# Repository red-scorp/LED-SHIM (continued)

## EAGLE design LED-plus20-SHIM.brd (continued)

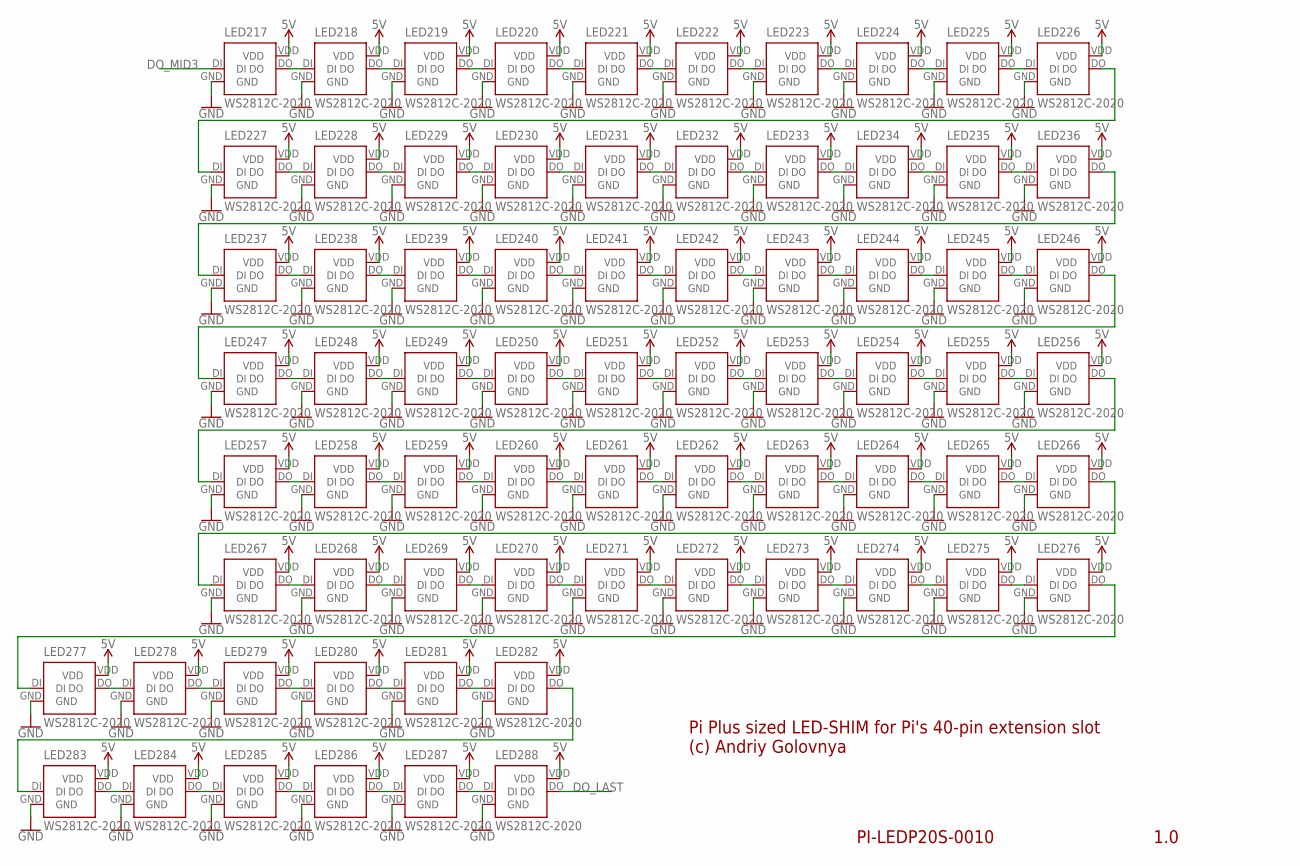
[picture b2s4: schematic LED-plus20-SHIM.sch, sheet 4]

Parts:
LED217, LED218, LED219, LED220, LED221, LED222, LED223, LED224, LED225, LED226, LED227, LED228, LED229, LED230, LED231, LED232, LED233, LED234, LED235, LED236, LED237, LED238, LED239, LED240, LED241, LED242, LED243, LED244, LED245, LED246, LED247, LED248, LED249, LED250, LED251, LED252, LED253, LED254, LED255, LED256, LED257, LED258, LED259, LED260, LED261, LED262, LED263, LED264, LED265, LED266, LED267, LED268, LED269, LED270, LED271, LED272, LED273, LED274, LED275, LED276, LED277, LED278, LED279, LED280, LED281, LED282, LED283, LED284, LED285, LED286, LED287, LED288: WS2812C-2020; WS2812X-2020

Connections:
5V: LED217.VDD, LED218.VDD, LED219.VDD, LED220.VDD, LED221.VDD, LED222.VDD, LED223.VDD, LED224.VDD, LED225.VDD, LED226.VDD, LED227.VDD, LED228.VDD, LED229.VDD, LED230.VDD, LED231.VDD, LED232.VDD, LED233.VDD, LED234.VDD, LED235.VDD, LED236.VDD, LED237.VDD, LED238.VDD, LED239.VDD, LED240.VDD, LED241.VDD, LED242.VDD, LED243.VDD, LED244.VDD, LED245.VDD, LED246.VDD, LED247.VDD, LED248.VDD, LED249.VDD, LED250.VDD, LED251.VDD, LED252.VDD, LED253.VDD, LED254.VDD, LED255.VDD, LED256.VDD, LED257.VDD, LED258.VDD, LED259.VDD, LED260.VDD, LED261.VDD, LED262.VDD, LED263.VDD, LED264.VDD, LED265.VDD, LED266.VDD, LED267.VDD, LED268.VDD, LED269.VDD, LED270.VDD, LED271.VDD, LED272.VDD, LED273.VDD, LED274.VDD, LED275.VDD, LED276.VDD, LED277.VDD, LED278.VDD, LED279.VDD, LED280.VDD, LED281.VDD, LED282.VDD, LED283.VDD, LED284.VDD, LED285.VDD, LED286.VDD, LED287.VDD, LED288.VDD; also elsewhere on the board
DO_LAST: LED288.DO; also elsewhere on the board
DO_MID3: LED217.DI; also elsewhere on the board
GND: LED217.GND, LED218.GND, LED219.GND, LED220.GND, LED221.GND, LED222.GND, LED223.GND, LED224.GND, LED225.GND, LED226.GND, LED227.GND, LED228.GND, LED229.GND, LED230.GND, LED231.GND, LED232.GND, LED233.GND, LED234.GND, LED235.GND, LED236.GND, LED237.GND, LED238.GND, LED239.GND, LED240.GND, LED241.GND, LED242.GND, LED243.GND, LED244.GND, LED245.GND, LED246.GND, LED247.GND, LED248.GND, LED249.GND, LED250.GND, LED251.GND, LED252.GND, LED253.GND, LED254.GND, LED255.GND, LED256.GND, LED257.GND, LED258.GND, LED259.GND, LED260.GND, LED261.GND, LED262.GND, LED263.GND, LED264.GND, LED265.GND, LED266.GND, LED267.GND, LED268.GND, LED269.GND, LED270.GND, LED271.GND, LED272.GND, LED273.GND, LED274.GND, LED275.GND, LED276.GND, LED277.GND, LED278.GND, LED279.GND, LED280.GND, LED281.GND, LED282.GND, LED283.GND, LED284.GND, LED285.GND, LED286.GND, LED287.GND, LED288.GND; also elsewhere on the board
unnamed: LED217.DO, LED218.DI
unnamed: LED218.DO, LED219.DI
unnamed: LED219.DO, LED220.DI
unnamed: LED220.DO, LED221.DI
unnamed: LED221.DO, LED222.DI
unnamed: LED222.DO, LED223.DI
unnamed: LED223.DO, LED224.DI
unnamed: LED224.DO, LED225.DI
unnamed: LED225.DO, LED226.DI
unnamed: LED226.DO, LED227.DI
unnamed: LED227.DO, LED228.DI
unnamed: LED228.DO, LED229.DI
unnamed: LED229.DO, LED230.DI
unnamed: LED230.DO, LED231.DI
unnamed: LED231.DO, LED232.DI
unnamed: LED232.DO, LED233.DI
unnamed: LED233.DO, LED234.DI
unnamed: LED234.DO, LED235.DI
unnamed: LED235.DO, LED236.DI
unnamed: LED236.DO, LED237.DI
unnamed: LED237.DO, LED238.DI
unnamed: LED238.DO, LED239.DI
unnamed: LED239.DO, LED240.DI
unnamed: LED240.DO, LED241.DI
unnamed: LED241.DO, LED242.DI
unnamed: LED242.DO, LED243.DI
unnamed: LED243.DO, LED244.DI
unnamed: LED244.DO, LED245.DI
unnamed: LED245.DO, LED246.DI
unnamed: LED246.DO, LED247.DI
unnamed: LED247.DO, LED248.DI
unnamed: LED248.DO, LED249.DI
unnamed: LED249.DO, LED250.DI
unnamed: LED250.DO, LED251.DI
unnamed: LED251.DO, LED252.DI
unnamed: LED252.DO, LED253.DI
unnamed: LED253.DO, LED254.DI
unnamed: LED254.DO, LED255.DI
unnamed: LED255.DO, LED256.DI
unnamed: LED256.DO, LED257.DI
unnamed: LED257.DO, LED258.DI
unnamed: LED258.DO, LED259.DI
unnamed: LED259.DO, LED260.DI
unnamed: LED260.DO, LED261.DI
unnamed: LED261.DO, LED262.DI
unnamed: LED262.DO, LED263.DI
unnamed: LED263.DO, LED264.DI
unnamed: LED264.DO, LED265.DI
unnamed: LED265.DO, LED266.DI
unnamed: LED266.DO, LED267.DI
unnamed: LED267.DO, LED268.DI
unnamed: LED268.DO, LED269.DI
unnamed: LED269.DO, LED270.DI
unnamed: LED270.DO, LED271.DI
unnamed: LED271.DO, LED272.DI
unnamed: LED272.DO, LED273.DI
unnamed: LED273.DO, LED274.DI
unnamed: LED274.DO, LED275.DI
unnamed: LED275.DO, LED276.DI
unnamed: LED276.DO, LED277.DI
unnamed: LED277.DO, LED278.DI
unnamed: LED278.DO, LED279.DI
unnamed: LED279.DO, LED280.DI
unnamed: LED280.DO, LED281.DI
unnamed: LED281.DO, LED282.DI
unnamed: LED282.DO, LED283.DI
unnamed: LED283.DO, LED284.DI
unnamed: LED284.DO, LED285.DI
unnamed: LED285.DO, LED286.DI
unnamed: LED286.DO, LED287.DI
unnamed: LED287.DO, LED288.DI

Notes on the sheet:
1.0
PI-LEDP20S-0010
Pi Plus sized LED-SHIM for Pi's 40-pin extension slot (c) Andriy Golovnya

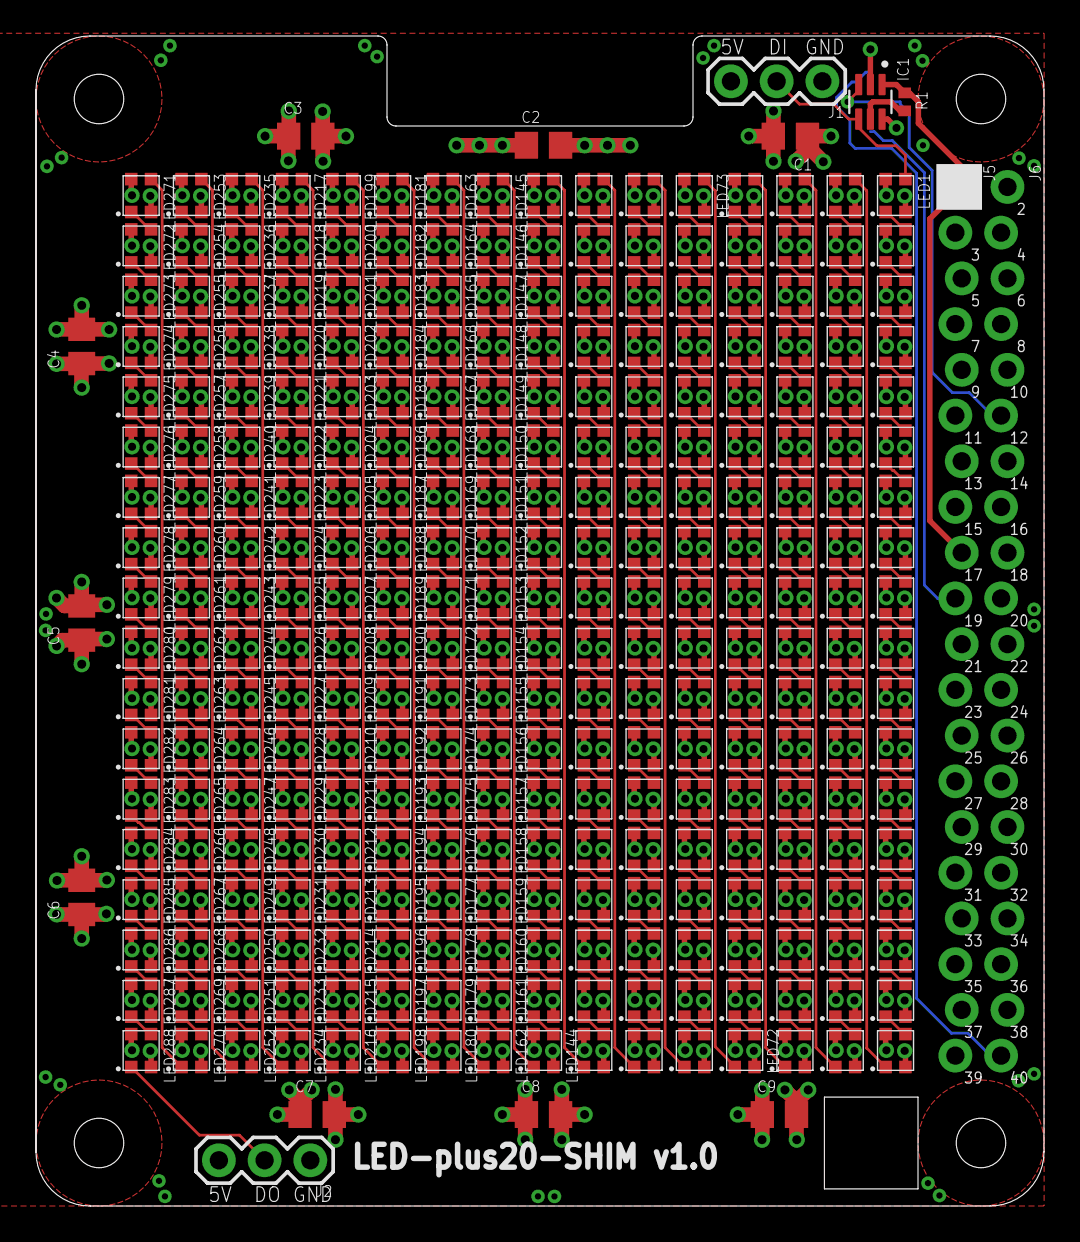
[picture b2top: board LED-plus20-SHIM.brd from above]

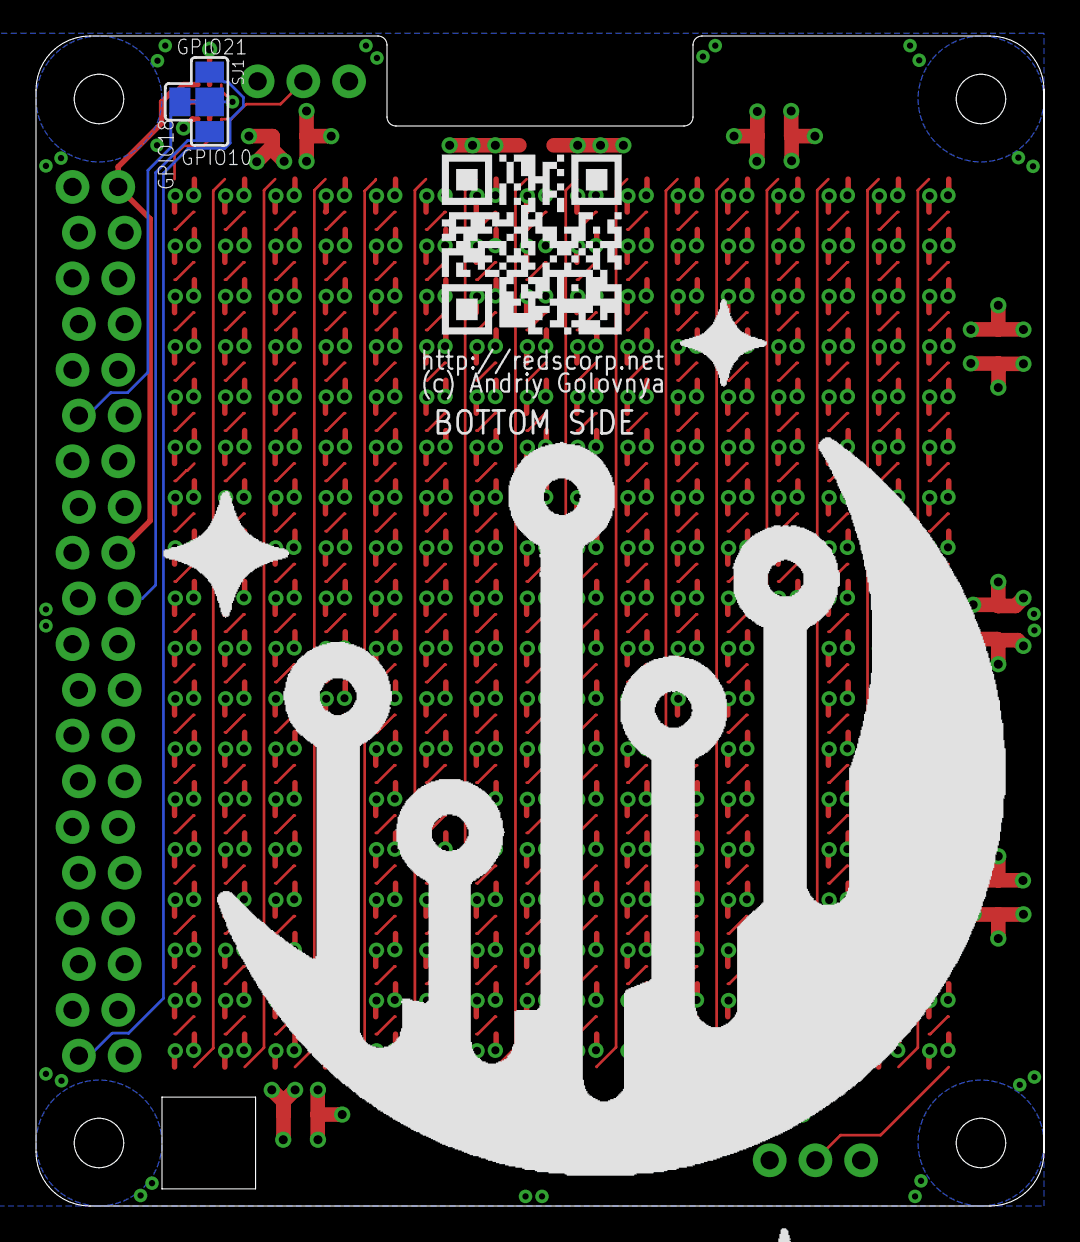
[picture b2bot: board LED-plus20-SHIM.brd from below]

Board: 4 copper layers, 56.0 x 65.0 mm, 306 parts (3 on the bottom side), 297 nets.

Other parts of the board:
LOGO3: RSNURL_QR_10MM

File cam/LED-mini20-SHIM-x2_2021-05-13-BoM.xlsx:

Qty | Designator | Footprint | Comment | LCSC Part #
2 | R1, R2 | 0402 | 10K | C25744
4 | C1, C2, C3, C4 | 0805 | 10uF | C15850
2 | IC1, IC2 | SC-70-6 | TXB0101DCKR | C324081
36 | LED1, LED2, LED3, LED4, LED5, LED6, LED7, LED8, LED9, LED10, LED11, LED12, LED1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 | LED-4_2.0x2.0x1.1P | WS2812C-2020 | C965556

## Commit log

2021-05-10 Added initial LED-zero-SHIM board design.
2021-05-11 added buffer and caps
2021-05-11 Added solder joint for DATA input configuration
2021-05-12 Use C veriant of LED insted of B.
2021-05-12 Added some traces.
2021-05-13 Made the board 4-layer and routed it completely.
2021-05-13 Generated PDF schematics.
2021-05-13 Generated PDF preview.
2021-05-13 Generated CAM, BoM, PnP files.
2021-05-13 Add github FUNDING file.
2021-05-13 Moved few traces around for better power delivery. Generated new CAM files.
2021-05-13 changed R1 rotation
2021-05-13 Added LED-mini-SHIM board.
2021-05-13 Generated PNG preview.
2021-05-15 Fixed parts orientation in PnP file.
2021-05-15 Added panelized version of LED-mini-SHIM board. Generated CAM, BoM and PnP files.
2021-05-16 Removed holes. Generated new CAM files.
2021-05-21 Moved some traces and vias around
2021-05-21 Generated new CAM files
2021-05-21 Generated PNG preview
2021-05-21 Generated CAM files
2021-06-07 Fixed some traces on zero SHIM. Generated PNG preview. Generated CAM files.
2021-06-07 Added base of plus board.
2021-06-07 Fixed some texts
2021-06-08 Finished tracing plus SHIM board.
2021-06-09 Moved few traces around.
2021-06-09 Generated PDF schematics
2021-06-10 Generated BoM file. Generated PnP file.
2021-06-11 Added few vias
2021-06-21 Updated descriptions
2021-06-29 Renamed files
2021-06-29 Updated texts. Generated CAM files. Generated PNG preview. Generated PDF schematics.
2021-06-29 Added mini35 board.
2021-06-29 Generated CAM files. Generated PNG preview. Generated PDF schematics.
2021-06-30 Cleaned mounting hole screwing area of copper. Generated CAM files.
2021-07-27 Added one more 35mm LED to the mini-board. Generated CAM files. Generated PDF schematics. Generated PNG preview.
2021-07-27 Updated descriptions.
2021-07-29 Make round cutouts in screwing area. Generated CAM files. Generated PNG previews.
2021-09-03 Generated BoM and PnP files.
2021-09-03 Updated description.
2021-09-03 Fixed VIA. Generated CAM files. Generated PNG preview. Renamed BoM and PnP files.
2021-09-03 Added x2 version of mini35 board. Generated CAM files.
2021-09-04 Added 35mm LDE zero board. Generated CAM files. Generated PNG preview. Generated PDF schematics.
2021-09-06 Base of 35mm size LED board.
2021-09-07 Routed 35 plus board. Generated CAM files. Generated PNG preview. Generated PDF schematics.
2021-09-10 Fixed x2 mini35 BoM.
2021-09-10 Generated BoM and PnP files for plus35 board.
2021-09-11 Fixed orientation of ws2812b-mini LEDs in PnP files. fixed naming of x2 BoM and PnP files.
2021-09-24 Added cut corner to ws2812b-mini footprint. Generated CAM files. Generated PNG preview.
2021-12-05 cleanup.
2022-01-24 Added Ko-Fi link
2023-08-28 Updated 'How to help' section.
